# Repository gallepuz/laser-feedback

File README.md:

# laser-feedback
Lab friendly Arduino/Nucleo shield for interfacing and feedback control of a pulsed laser ablator. It can be used in any application where a pulse's duration must be determined by an independent signal stemming from the subject that is recieving the pulse. 

### Build
The complete assembly requires procuring the following:
* PCB populated with components (we have spare unpopulated boards, [contact us](https://twitter.com/uSD_cardlord)!)
* Front panel (we also have spares, in black and green!)
* STM32 nucleo board, we used [this one](https://no.rs-online.com/web/p/microcontroller-development-tools/8644009?cm_mmc=NO-PLA-DS3A-_-google-_-CSS_NO_EN_Pmax_Test-_--_-8644009&matchtype=&&gad_source=1&gclid=Cj0KCQiA5rGuBhCnARIsAN11vgTcTMmP5npaGDRg-D278EnYeHQQxJDi09af2U7zakMZlYZ7tpOIE30aAnx8EALw_wcB&gclsrc=aw.ds)
* [Extruded aluminum enclosure](https://no.rs-online.com/web/p/general-purpose-enclosures/7732981/?redirect-relevancy-data=7365617263685F636173636164655F6F726465723D31267365617263685F696E746572666163655F6E616D653D4931384E525353746F636B4E756D626572267365617263685F6D617463685F6D6F64653D6D61746368616C6C267365617263685F7061747465726E5F6D6174636865643D5E2828282872737C5253295B205D3F293F285C647B337D5B5C2D5C735D3F5C647B332C347D5B705061415D3F29297C283235285C647B387D7C5C647B317D5C2D5C647B377D29292924267365617263685F747970653D52535F53544F434B5F4E554D424552267365617263685F77696C645F63617264696E675F6D6F64653D4E4F4E45267365617263685F6B6579776F72643D3737332D32393831267365617263685F6B6579776F72645F6170703D3737333239383126)
* 3x 11mm long M3 [standoffs](https://no.rs-online.com/web/p/standoffs/1768393/?redirect-relevancy-data=7365617263685F636173636164655F6F726465723D31267365617263685F696E746572666163655F6E616D653D4931384E525353746F636B4E756D626572267365617263685F6D617463685F6D6F64653D6D61746368616C6C267365617263685F7061747465726E5F6D6174636865643D5E2828282872737C5253295B205D3F293F285C647B337D5B5C2D5C735D3F5C647B332C347D5B705061415D3F29297C283235285C647B387D7C5C647B317D5C2D5C647B377D29292924267365617263685F747970653D52535F53544F434B5F4E554D424552267365617263685F77696C645F63617264696E675F6D6F64653D4E4F4E45267365617263685F6B6579776F72643D3137362D38333933267365617263685F6B6579776F72645F6170703D3137363833393326) preferably nylon but these were in stock back then...
* 6x 5mm long M3 [screws](https://no.rs-online.com/web/p/machine-screws/1854400/?redirect-relevancy-data=7365617263685F636173636164655F6F726465723D31267365617263685F696E746572666163655F6E616D653D4931384E525353746F636B4E756D626572267365617263685F6D617463685F6D6F64653D6D61746368616C6C267365617263685F7061747465726E5F6D6174636865643D5E2828282872737C5253295B205D3F293F285C647B337D5B5C2D5C735D3F5C647B332C347D5B705061415D3F29297C283235285C647B387D7C5C647B317D5C2D5C647B377D29292924267365617263685F747970653D52535F53544F434B5F4E554D424552267365617263685F77696C645F63617264696E675F6D6F64653D4E4F4E45267365617263685F6B6579776F72643D3138352D34343030267365617263685F6B6579776F72645F6170703D3138353434303026)
* [Optional] 1x [16 pin DIP socket](https://no.rs-online.com/web/p/dil-sockets/0813137)
* [Optional] 1x [8 pin DIP socket](https://no.rs-online.com/web/p/dil-sockets/0813115)
---

### Use
The output is active high by design and cannot be changed to active low.
1. Connect the artifact to your computer using a USB A to mini B. The front panel backlight will come on. Do not press "ARM". The "Pulse active" and "Arm" LEDs should both be off.
2. Open a USB serial port and set the baud rate to 38400. Adjust the comparator cutoff value and send other configuration commands (need to add more details on this).
3. Connect your setup to the input and output. 
4. Press the square ARM button to enable the output.

**To disarm** the output you need to power cycle the device or press the reset button. Once it is armed it cannot be disarmed. This is by design of the output enable safety failsafe.

---

### Output enable failsafe
Working with lasers can be dangerous, [specially if you cannot see them](https://en.wikipedia.org/wiki/Laser_safety#Safety_measures). So we put effort into designing in a simple circuit that will prevent the device from driving whatever is connected to the output unless it is manually armed by the user first. We achieve this by floating the output with the help of a relay and a spare latch on the 74LS279. With the help of pull resistors and two NPNs we also implement a simple mechanism that prevents the user from arming if the output is high at that time. 

This circuit is thus not controlled by software and will act the same way upon power up every time. 

---

### DTU unit notes
The unit at DTU does not have an identifier at the moment. Its enclosure is not grounded so the green and yellow post is effectively floating.

---

### Grounding the enclosure
On the front panel there is a solid copper path between the BNCs and the corner holes can provide an effective faraday cage to the whole assembly. We say *can* because we haven't tested this. The top right and bottom left can be used to ground the enclosure to the electronics within. The plated region around the input and output holes connects to the washer on the BNC connector but not the shield (at least on the BNC in BOM). The binding post can be used to choose where the enclosure is connected and whether it is connected to system ground if desired. Should add pictures... 

To secure grounding of the enclosure unscrew one of the corner panel screws and place a (conductive) washer.  

---

### Disconnecting the BNC shield - enclosure shunt
By default the shielding on the BNC is connected to the *enclosure and system ground* via the plated rings on the front panel screws and R9 and R8 on the PCB respectively.
- To disconnect the shield further, R8 and R9 can be desoldered.
Doing both of these will float the shielding. Do it partially on one or both BNC connectors to get other configurations.

---

### Known issues
- When the diodes are installed the comparator output is forced high. The diodes present in this BOM are ESD diodes rather than rectifier diodes and are likely the culprit. Removing them fixes the problem. We keep in mind this effectively removes overvoltage protection and 3V3 ADC boards might be damaged if there is no proper control over the photodiode signal amplitude.
- The front panel says this is a PLL, it is not. We forgot to remove it after moving away from another idea...

---

### To Do
Add pictures of grounding.
Eventually deixar només els gerbers i un pdf de l'esquematic a la carpeta hardware.
Add more information on serial interface commands.

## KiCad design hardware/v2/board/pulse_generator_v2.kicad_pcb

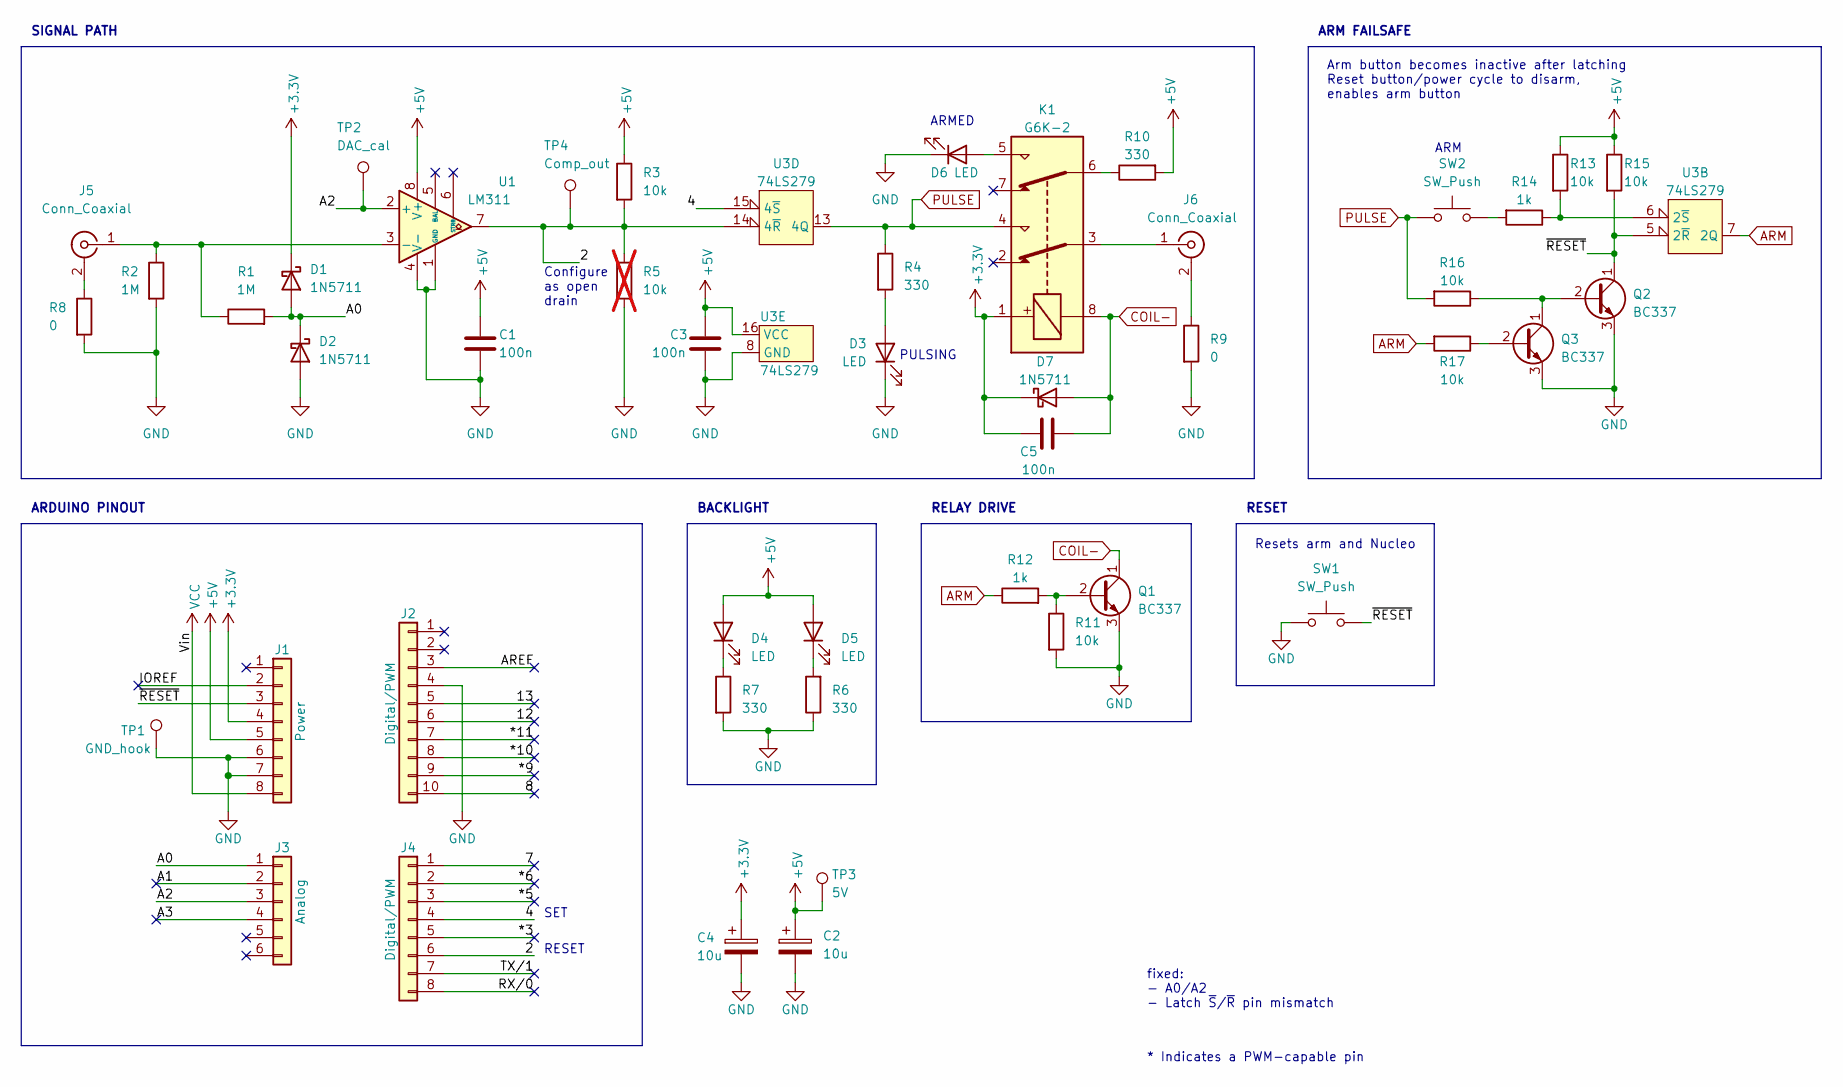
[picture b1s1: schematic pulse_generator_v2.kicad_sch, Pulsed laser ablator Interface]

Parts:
C1, C3, C5: 100n; C_0805_2012Metric_Pad1.18x1.45mm_HandSolder
C2, C4: 10u; CP_Radial_D5.0mm_P2.50mm
D1, D2, D7: 1N5711; D_SOD-123
D3, D4, D5, D6: LED; LED_D5.0mm
J1: Power; PinHeader_1x08_P2.54mm_Vertical
J2: Digital/PWM; PinHeader_1x10_P2.54mm_Vertical
J3: Analog; PinHeader_1x06_P2.54mm_Vertical
J4: Digital/PWM; PinHeader_1x08_P2.54mm_Vertical
J5, J6: Conn_Coaxial; BNC_Amphenol_B6252HB-NPP3G-50_Horizontal
K1: G6K-2; Relay_DPDT_Omron_G6K-2F-Y
Q1, Q2, Q3: BC337; TO-92_Inline_Wide
R1, R2: 1M; R_0805_2012Metric_Pad1.20x1.40mm_HandSolder
R3, R11, R13, R15, R16, R17: 10k; R_0805_2012Metric_Pad1.20x1.40mm_HandSolder
R4, R6, R7, R10: 330; R_0805_2012Metric_Pad1.20x1.40mm_HandSolder
R5: 10k; R_0805_2012Metric_Pad1.20x1.40mm_HandSolder; not fitted
R8, R9: 0; R_0805_2012Metric_Pad1.20x1.40mm_HandSolder
R12, R14: 1k; R_0805_2012Metric_Pad1.20x1.40mm_HandSolder
SW1, SW2: SW_Push; SW_Tactile_SPST_Angled_PTS645Vx39-2LFS
TP1: GND_hook; PinHeader_1x01_P2.54mm_Vertical
TP2: DAC_cal; PinHeader_1x01_P2.54mm_Vertical
TP3: 5V; PinHeader_1x01_P2.54mm_Vertical
TP4: Comp_out; PinHeader_1x01_P2.54mm_Vertical
U1: LM311; DIP-8_W7.62mm_Socket_LongPads
U3: 74LS279; DIP-16_W7.62mm_Socket_LongPads

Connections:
+3V3: C4.1, C5.1, D1.1 (K), D7.1 (K), J1.4, K1.1
+5V: C1.1, C2.1, C3.1, D4.2 (A), D5.2 (A), J1.5, R3.1, R10.2, R13.1, R15.1, TP3.1, U1.8 (V+), U3.16 (VCC)
/2: J4.6, R3.2, R5.1, TP4.1, U1.7, U3.14 (4~R)
/4: J4.4, U3.15 (4~S)
/7: J4.1
/8: J2.10
/12: J2.6
/13: J2.5
/*3: J4.5
/*5: J4.3
/*6: J4.2
/*9: J2.9
/*10: J2.8
/*11: J2.7
/A0: D1.2 (A), D2.1 (K), J3.1, R1.2
/A1: J3.2
/A2: J3.3, TP2.1, U1.2 (+)
/A3: J3.4
/AREF: J2.3
/IOREF: J1.2
/RX/0: J4.8
/TX/1: J4.7
/~RESET: J1.3, Q2.1 (C), R15.2, SW1.2, U3.5 (2~R)
ARM: R12.1, R17.2, U3.7 (2Q)
COIL-: C5.2, D7.2 (A), K1.8, Q1.1 (C)
GND: C1.2, C2.2, C3.2, C4.2, D2.2 (A), D3.1 (K), D6.1 (K), J1.6, J1.7, J2.4, Q1.3 (E), Q2.3 (E), Q3.3 (E), R2.2, R5.2, R6.1, R7.2, R8.2, R9.2, R11.2, SW1.1, TP1.1, U1.1 (GND), U1.4 (V-), U3.8 (GND); also elsewhere on the board
unnamed: D3.2 (A), R4.2
unnamed: D4.1 (K), R7.1
unnamed: D5.1 (K), R6.2
unnamed: D6.2 (A), K1.5
unnamed: J5.2 (Ext), R8.1
unnamed: J5.1 (In), R1.1, R2.1, U1.3 (-)
unnamed: J6.2 (Ext), R9.1
unnamed: J6.1 (In), K1.3
unnamed: K1.6, R10.1
unnamed: Q1.2 (B), R11.1, R12.2
unnamed: Q2.2 (B), Q3.1 (C), R16.1
unnamed: Q3.2 (B), R17.1
unnamed: R14.2, SW2.2
unnamed: R13.2, R14.1, U3.6 (2~S)
PULSE: K1.4, R4.1, R16.2, SW2.1, U3.13 (4Q)
VCC: J1.8

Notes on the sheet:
ARM
ARMED
SET
BACKLIGHT
Configure as open drain
ARDUINO PINOUT
Arm button becomes inactive after latching Reset button/power cycle to disarm, enables arm button
RESET
SIGNAL PATH
ARM FAILSAFE
RELAY DRIVE
fixed: - A0/A2 - Latch ~{S}/~{R} pin mismatch
Resets arm and Nucleo
* Indicates a PWM-capable pin
PULSING

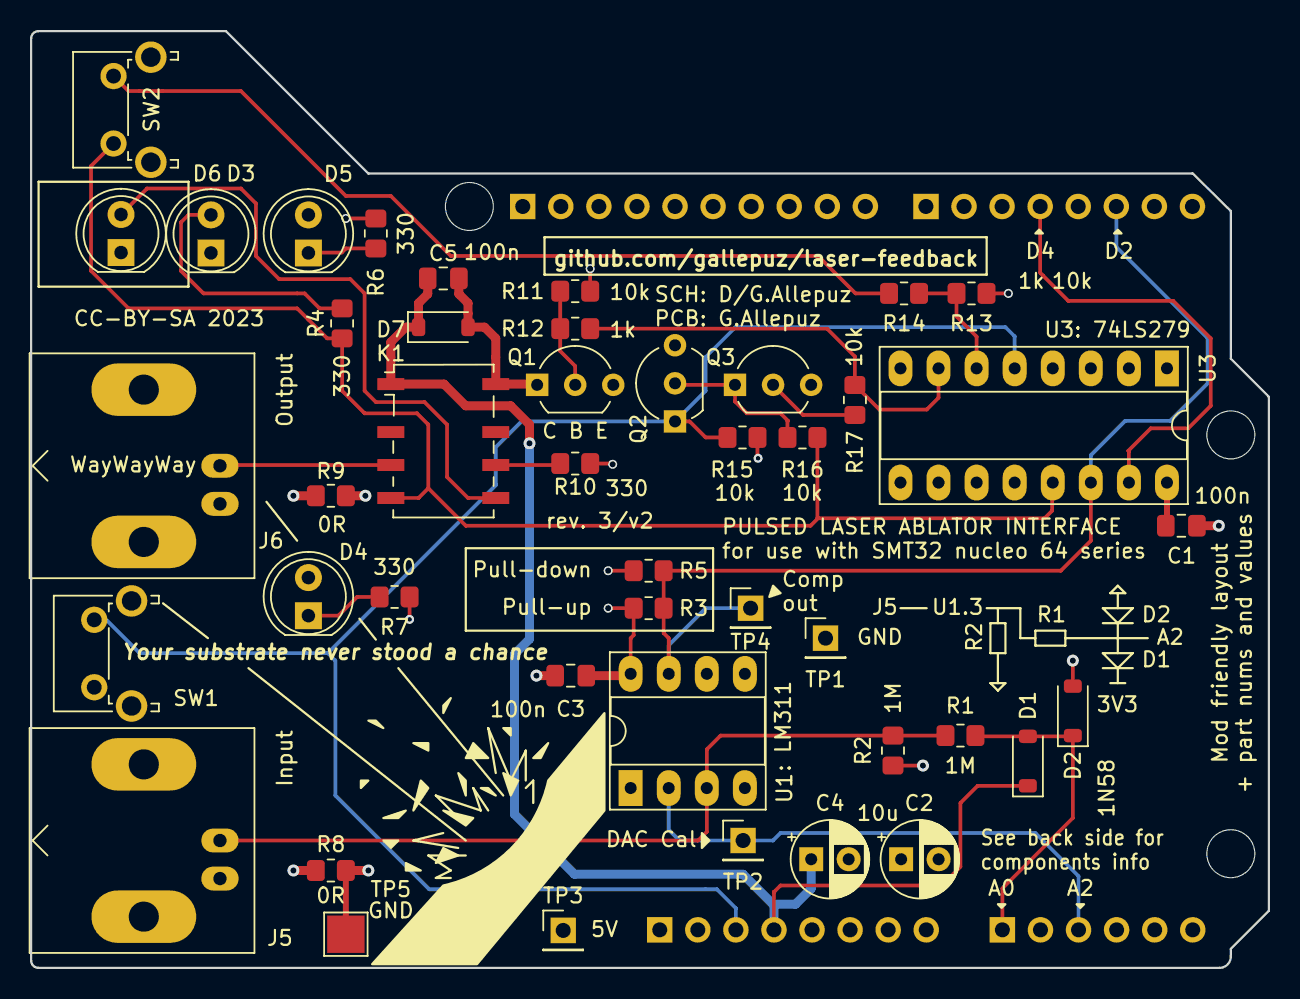
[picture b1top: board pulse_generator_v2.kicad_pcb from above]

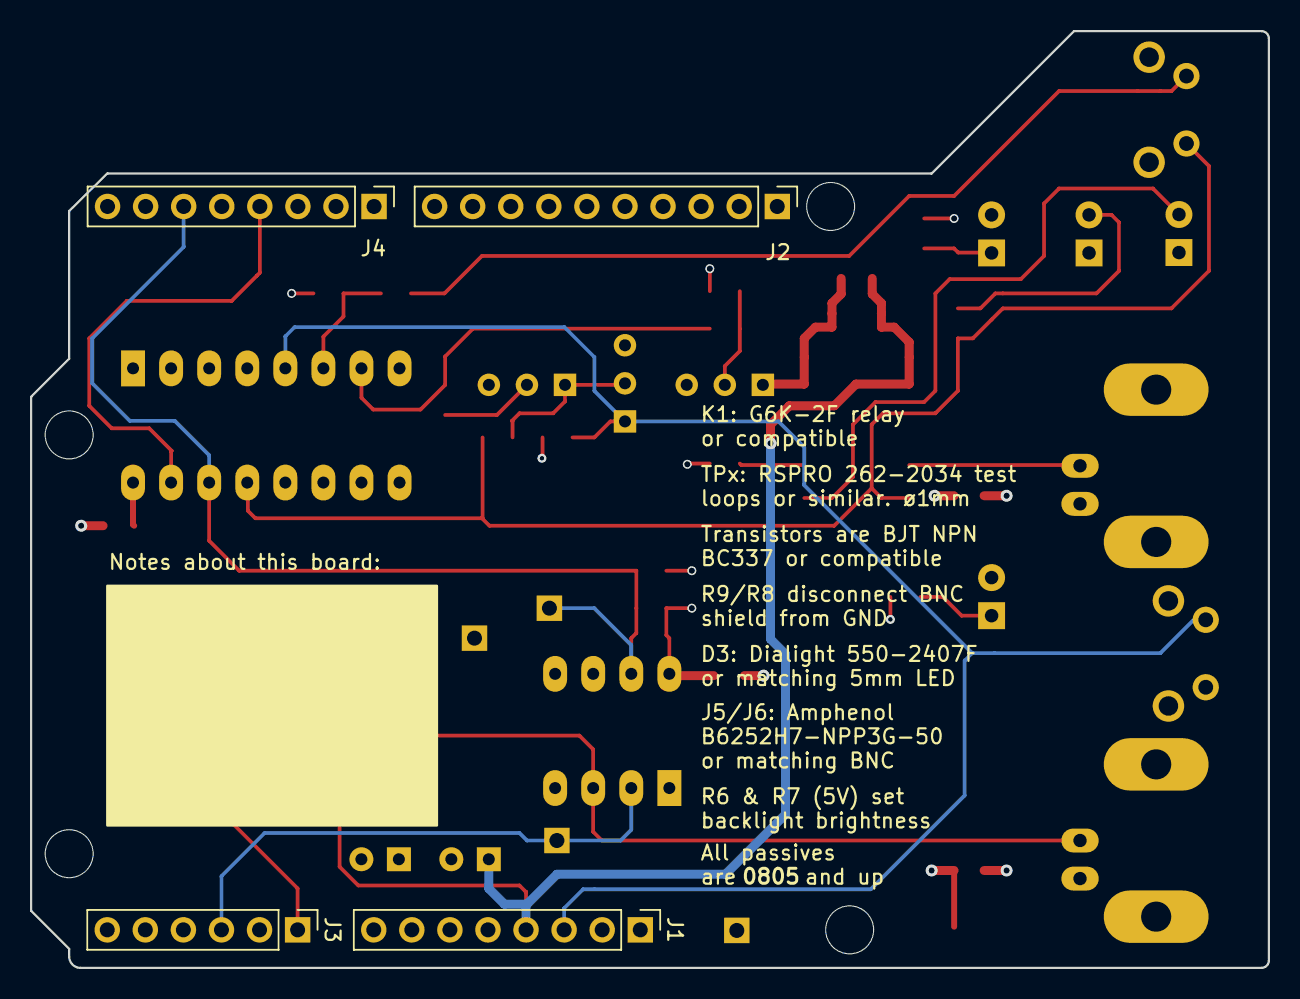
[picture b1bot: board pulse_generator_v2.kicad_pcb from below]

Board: 4 copper layers, 82.6 x 62.5 mm, 52 parts (4 on the bottom side), 25 nets.

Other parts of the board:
MH1, MH2, MH3, MH4: MountingHole_3.2mm
TP5: GND_pad; TestPoint_Pad_2.5x2.5mm

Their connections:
GND: TP5.1; also elsewhere on the board

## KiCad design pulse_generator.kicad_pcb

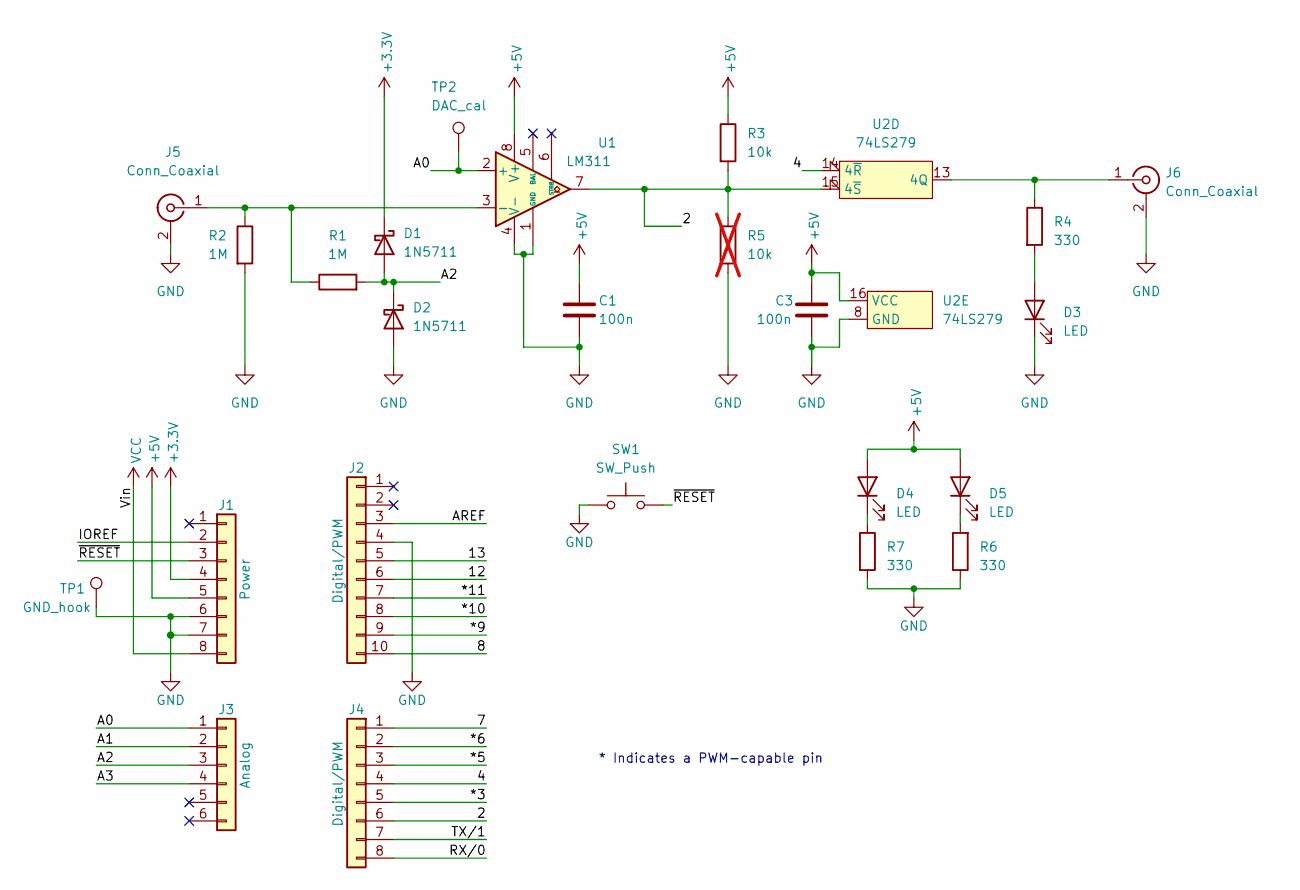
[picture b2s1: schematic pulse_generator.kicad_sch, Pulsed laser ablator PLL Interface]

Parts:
C1, C3: 100n; C_0805_2012Metric_Pad1.18x1.45mm_HandSolder
D1, D2: 1N5711; D_SOD-123
D3: LED; LED_D5.0mm
D4, D5: LED; LED_0805_2012Metric_Pad1.15x1.40mm_HandSolder
J1: Power; PinHeader_1x08_P2.54mm_Vertical
J2: Digital/PWM; PinHeader_1x10_P2.54mm_Vertical
J3: Analog; PinHeader_1x06_P2.54mm_Vertical
J4: Digital/PWM; PinHeader_1x08_P2.54mm_Vertical
J5, J6: Conn_Coaxial; BNC_Amphenol_B6252HB-NPP3G-50_Horizontal
R1, R2: 1M; R_0805_2012Metric_Pad1.20x1.40mm_HandSolder
R3: 10k; R_0805_2012Metric_Pad1.20x1.40mm_HandSolder
R4, R6, R7: 330; R_0805_2012Metric_Pad1.20x1.40mm_HandSolder
R5: 10k; R_0805_2012Metric_Pad1.20x1.40mm_HandSolder; not fitted
SW1: SW_Push; SW_Tactile_SPST_Angled_PTS645Vx39-2LFS
TP1: GND_hook; PinHeader_1x01_P2.54mm_Vertical
TP2: DAC_cal; PinHeader_1x01_P2.54mm_Vertical
U1: LM311; DIP-8_W7.62mm_Socket_LongPads
U2: 74LS279; DIP-16_W7.62mm_Socket_LongPads

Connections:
+3V3: D1.1 (K), J1.4
+5V: C1.1, C3.1, D4.2 (A), D5.2 (A), J1.5, R3.1, U1.8 (V+), U2.16 (VCC)
/2: J4.6, R3.2, R5.1, U1.7, U2.15 (4~S)
/4: J4.4, U2.14 (4~R)
/7: J4.1
/8: J2.10
/12: J2.6
/13: J2.5
/*3: J4.5
/*5: J4.3
/*6: J4.2
/*9: J2.9
/*10: J2.8
/*11: J2.7
/A0: J3.1, TP2.1, U1.2 (+)
/A1: J3.2
/A2: D1.2 (A), D2.1 (K), J3.3, R1.2
/A3: J3.4
/AREF: J2.3
/IOREF: J1.2
/RX/0: J4.8
/TX/1: J4.7
/~RESET: J1.3, SW1.2
unnamed: D3.2 (A), R4.2
unnamed: D4.1 (K), R7.1
unnamed: D5.1 (K), R6.2
unnamed: J5.1 (In), R1.1, R2.1, U1.3 (-)
unnamed: J6.1 (In), R4.1, U2.13 (4Q)
VCC: J1.8

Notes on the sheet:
* Indicates a PWM-capable pin

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
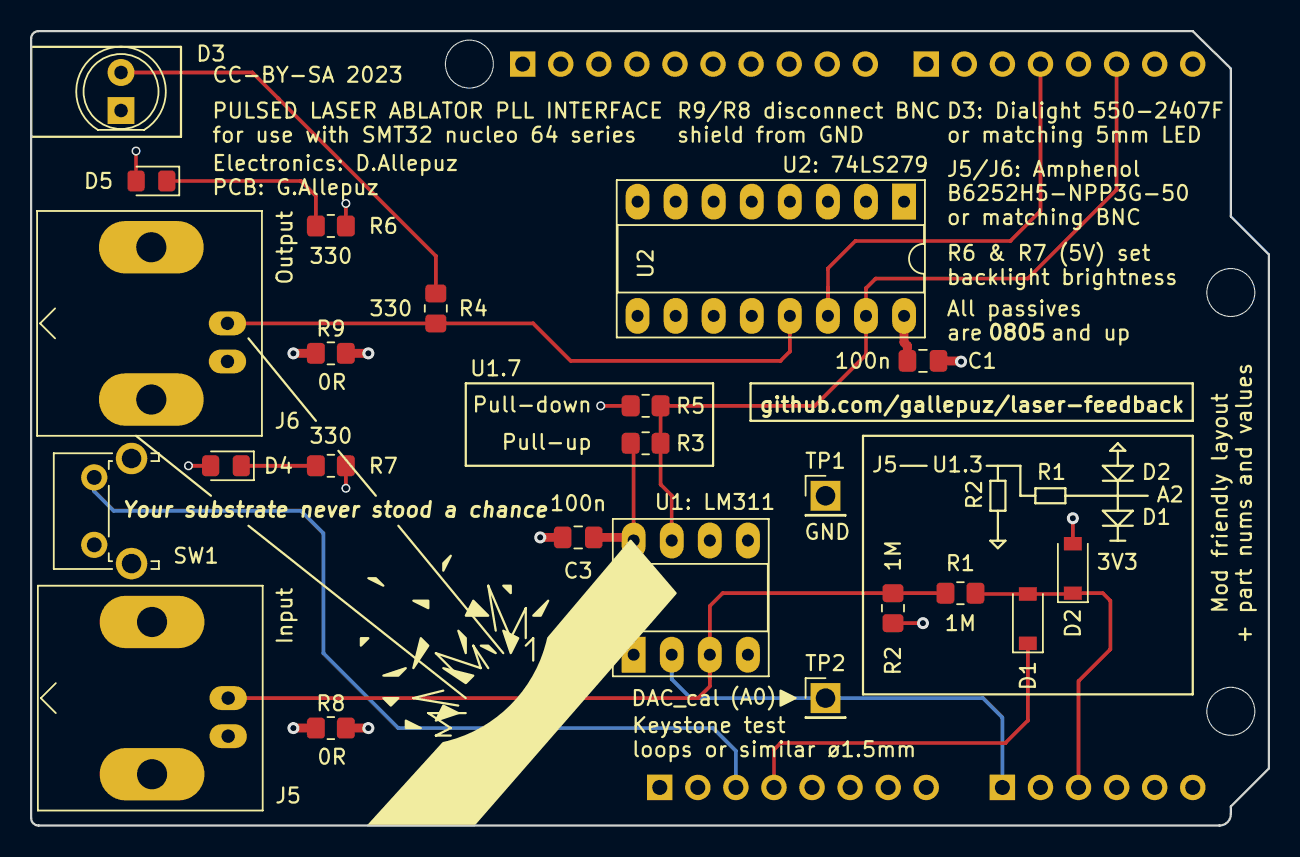
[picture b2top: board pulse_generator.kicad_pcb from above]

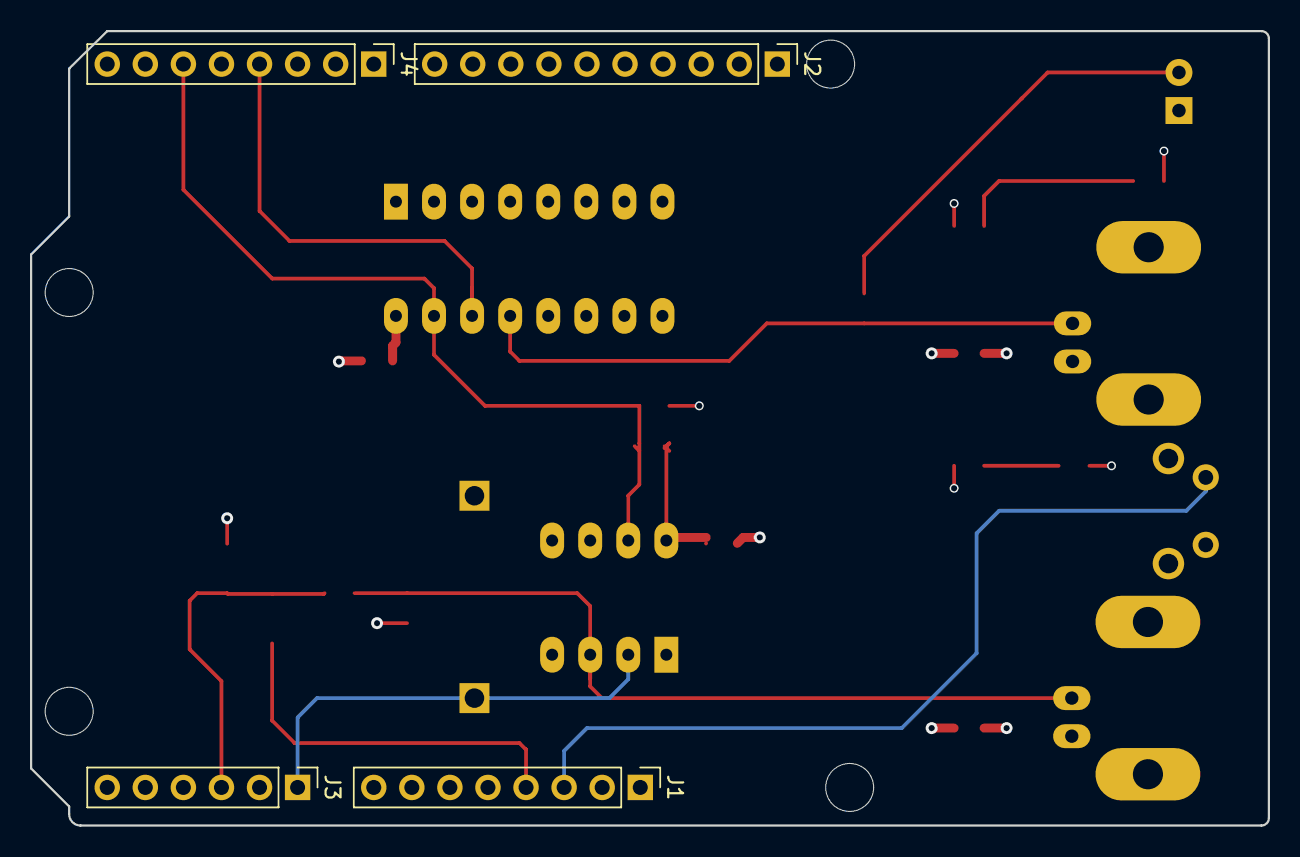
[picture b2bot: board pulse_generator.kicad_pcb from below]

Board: 4 copper layers, 82.6 x 53.0 mm, 31 parts (4 on the bottom side), 15 nets.

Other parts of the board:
MH1, MH2, MH3, MH4: MountingHole_3.2mm
R8, R9: 0; R_0805_2012Metric_Pad1.20x1.40mm_HandSolder

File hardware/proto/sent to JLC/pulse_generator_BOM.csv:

Comment,Designator,Footprint,JLCPCB Part #（optional）
1N5711,"D1,D2",D_SOD-123,C727115
DAC_cal,TP2,PinHeader_1x01_P2.54mm_Vertical,C238118
SW_Push,SW1,SW_Tactile_SPST_Angled_PTS645Vx39-2LFS,C266195
LED,D3,LED_D5.0mm,C3001995
330,"R7,R4,R6",R_0805_2012Metric_Pad1.20x1.40mm_HandSolder,C2984391
Conn_Coaxial,"J5,J6",BNC_Amphenol_B6252HB-NPP3G-50_Horizontal,C305920
LED,"D5,D4",LED_0805_2012Metric_Pad1.15x1.40mm_HandSolder,C497949
74LS279,U2,DIP-16_W7.62mm_Socket_LongPads,C3170693
0,"R8,R9",R_0805_2012Metric_Pad1.20x1.40mm_HandSolder,C346501
10k,"R3,R5",R_0805_2012Metric_Pad1.20x1.40mm_HandSolder,C84376
LM311,U1,DIP-8_W7.62mm_Socket_LongPads,C305904
1M,"R1,R2",R_0805_2012Metric_Pad1.20x1.40mm_HandSolder,C479091
GND_hook,TP1,PinHeader_1x01_P2.54mm_Vertical,C238118
100n,"C3,C1",C_0805_2012Metric_Pad1.18x1.45mm_HandSolder,C85866

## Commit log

2023-02-17 untracked files
2023-02-17 atchoo!
2023-02-18 decoupling lm311 update
2023-02-18 plot ready for review
2023-02-18 wrong comp pd value
2023-02-18 re-plotted
2023-02-19 sch rev2
2023-02-19 forgot to plot
2023-03-02 guardat amb og shield outline
2023-03-03 shield edge cuts save
2023-03-03 nucleo form factor
2023-05-23 Ready for review
    Ready for review
2023-05-23 forgot to plot again
2023-05-23 minor tweaks
2023-05-23 Added all assets and 3d models
2023-05-23 past commit failed to add untracked
2023-05-23 BNC copper padding clearance
2023-05-23 added how to ground
2023-05-24 corrected some stuff, larger enclosure
2023-05-24 changed "sleeve" for "shield"
2023-05-24 rearrange diode clamp section
2023-08-10 Please enter the commit message for your changes. Lines starting
2023-08-10 reorganisin
2023-08-10 obviously fd it
2023-08-10 added gitignore, firmware, tidy up
2023-08-10 deleted firmware zip
2023-08-10 readme touchup
2023-09-05 some changes related to testing
2023-09-05 moving stuff around, porting to 303RE
2023-09-13 code no pulse on reset + consistent failsafe time
2023-09-13 moving stuff around
2023-09-13 untracked hardware
2023-09-14 autosaves
2023-09-24 added pdf of v2 w relay circuit
2023-09-24 added untracked v2 pdf w relay circuit
2023-09-27 failsafe arm fixes
2023-10-11 added failsafe arm, mech fixes
2023-10-11 v2 hw with failsafe arm and mech fixes
2023-10-12 gerbers out
2023-11-18 first commit after final at DTU
2023-11-18 Update README.md
    some notes on usage
2023-11-18 remove outdated shielding indications
2024-02-14 Added picture and note on the diode limiter issue
2024-02-14 Update readme with some build info, more to come
2024-02-14 Same as last commit, formatting fixes
2024-02-15 Added use section and safety circuit explanation

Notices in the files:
hardware/v2/board/pulse_generator_v2.kicad_pcb:
CC-BY-SA 2023
